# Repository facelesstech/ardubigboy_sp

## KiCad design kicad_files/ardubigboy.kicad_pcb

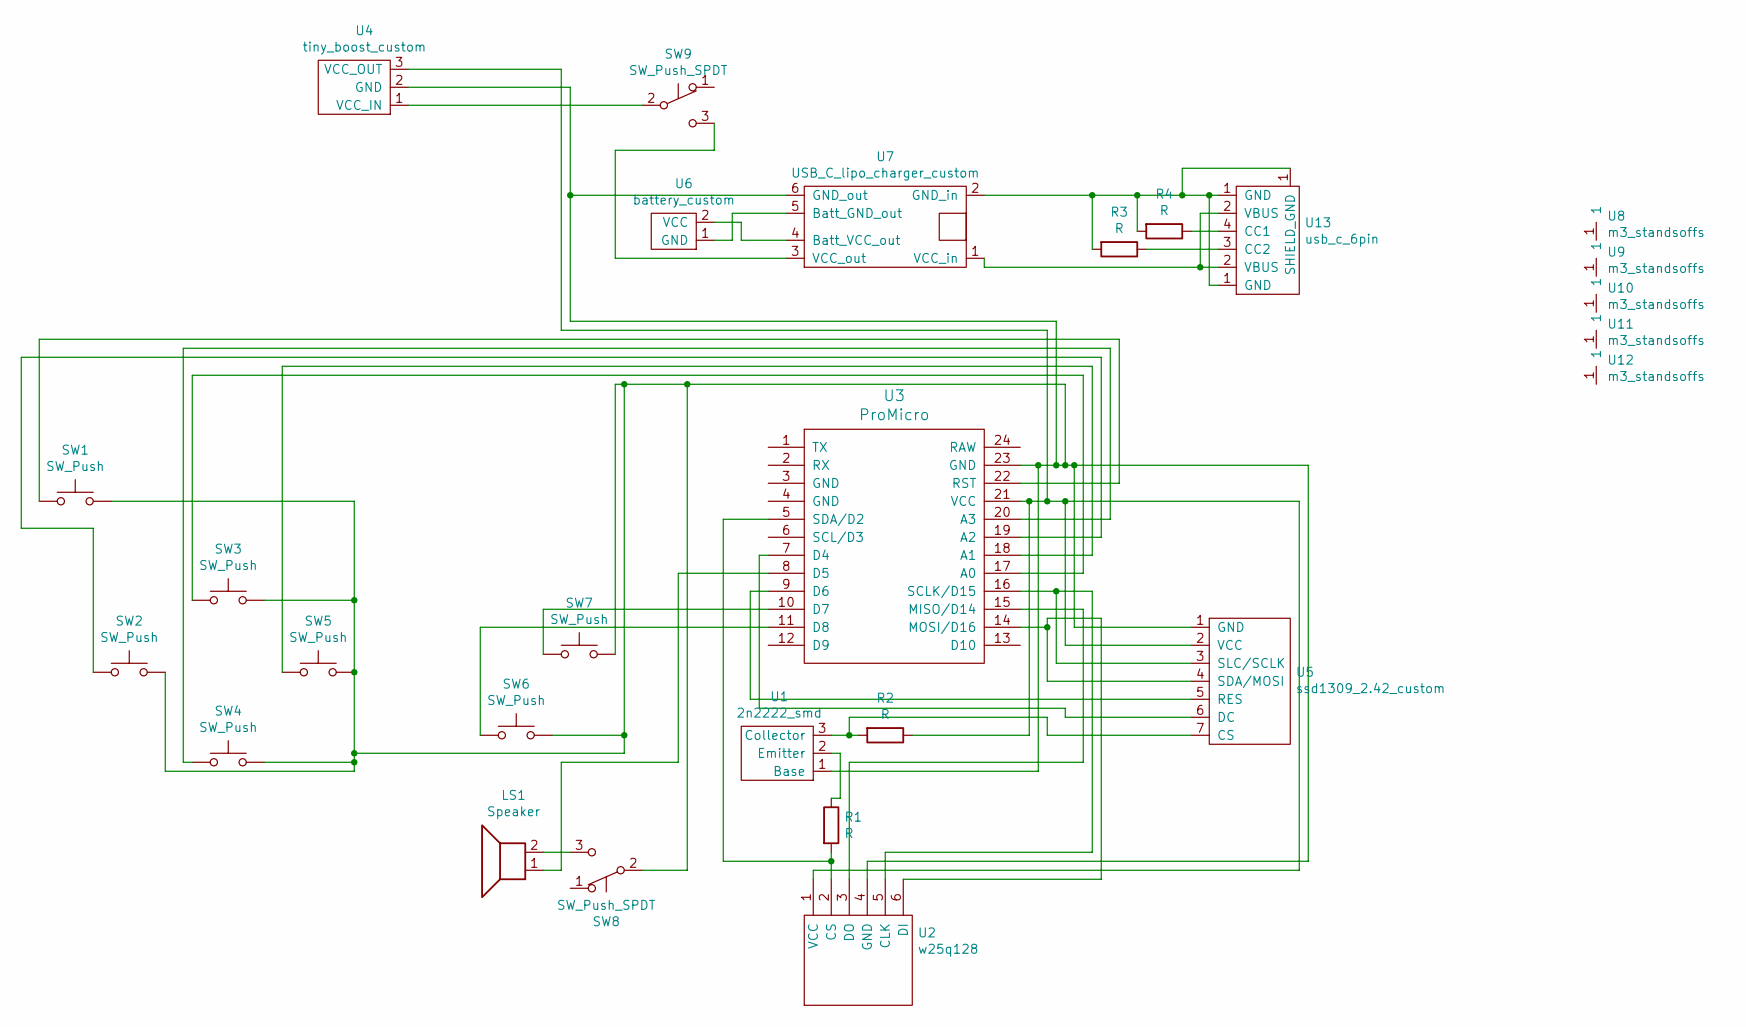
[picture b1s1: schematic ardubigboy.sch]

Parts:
LS1: Speaker; piezo_smd
R1, R2, R3, R4: R; R_1206_3216Metric_Pad1.42x1.75mm_HandSolder
SW1, SW2, SW3, SW4, SW5, SW6, SW7: SW_Push; dome_buttons_custom
SW8: SW_Push_SPDT; tiny_smd_slide_switch_adjustable
SW9: SW_Push_SPDT; 3_pin_switch_smd_side_mount
U1: 2n2222_smd; SOT-23_custom
U2: w25q128; W25Q128_smd_custom
U3: ProMicro; ProMicro_smd_pads
U4: tiny_boost_custom; Tiny_boost_orange_smd
U5: ssd1309_2.42_custom; ssd1309_2.42_custom_headers
U6: battery_custom; vcc_gnd_2pin_custom
U7: USB_C_lipo_charger_custom; USB_C_SMD_lipo_charger_custom
U8, U9, U10, U11, U12: m3_standsoffs; M4.5_custom
U13: usb_c_6pin; USB_C_6PIN_custom

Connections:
unnamed: LS1.1, U3.8 (D5)
unnamed: LS1.2, SW8.3 (C)
unnamed: R1.1, U1.2 (Emitter)
unnamed: R1.2, U2.2 (CS), U3.5 (SDA/D2)
unnamed: R2.1, U2.1 (VCC), U3.21 (VCC), U4.3 (VCC_OUT), U5.2 (VCC)
unnamed: R2.2, U1.3 (Collector), U5.7 (CS)
unnamed: R3.1, U13.3 (CC2)
unnamed: R3.2, R4.2, U7.2 (GND_in), U13.1 (GND)
unnamed: R4.1, U13.4 (CC1)
unnamed: SW1.1, U3.22 (RST)
unnamed: SW1.2, SW2.2, SW3.2, SW4.2, SW5.2, SW6.2, SW7.2, SW8.2 (B), U1.1 (Base), U2.4 (GND), U3.23 (GND), U4.2 (GND), U5.1 (GND), U7.6 (GND_out)
unnamed: SW2.1, U3.19 (A2)
unnamed: SW3.1, U3.17 (A0)
unnamed: SW4.1, U3.20 (A3)
unnamed: SW5.1, U3.18 (A1)
unnamed: SW6.1, U3.11 (D8)
unnamed: SW7.1, U3.10 (D7)
unnamed: SW9.2 (B), U4.1 (VCC_IN)
unnamed: SW9.3 (C), U7.3 (VCC_out)
unnamed: U2.3 (DO), U3.15 (MISO/D14)
unnamed: U2.5 (CLK), U3.16 (SCLK/D15), U5.3 (SLC/SCLK)
unnamed: U2.6 (DI), U3.14 (MOSI/D16), U5.4 (SDA/MOSI)
unnamed: U3.7 (D4), U5.6 (DC)
unnamed: U3.9 (D6), U5.5 (RES)
unnamed: U6.1 (GND), U7.5 (Batt_GND_out)
unnamed: U6.2 (VCC), U7.4 (Batt_VCC_out)
unnamed: U7.1 (VCC_in), U13.2 (VBUS)

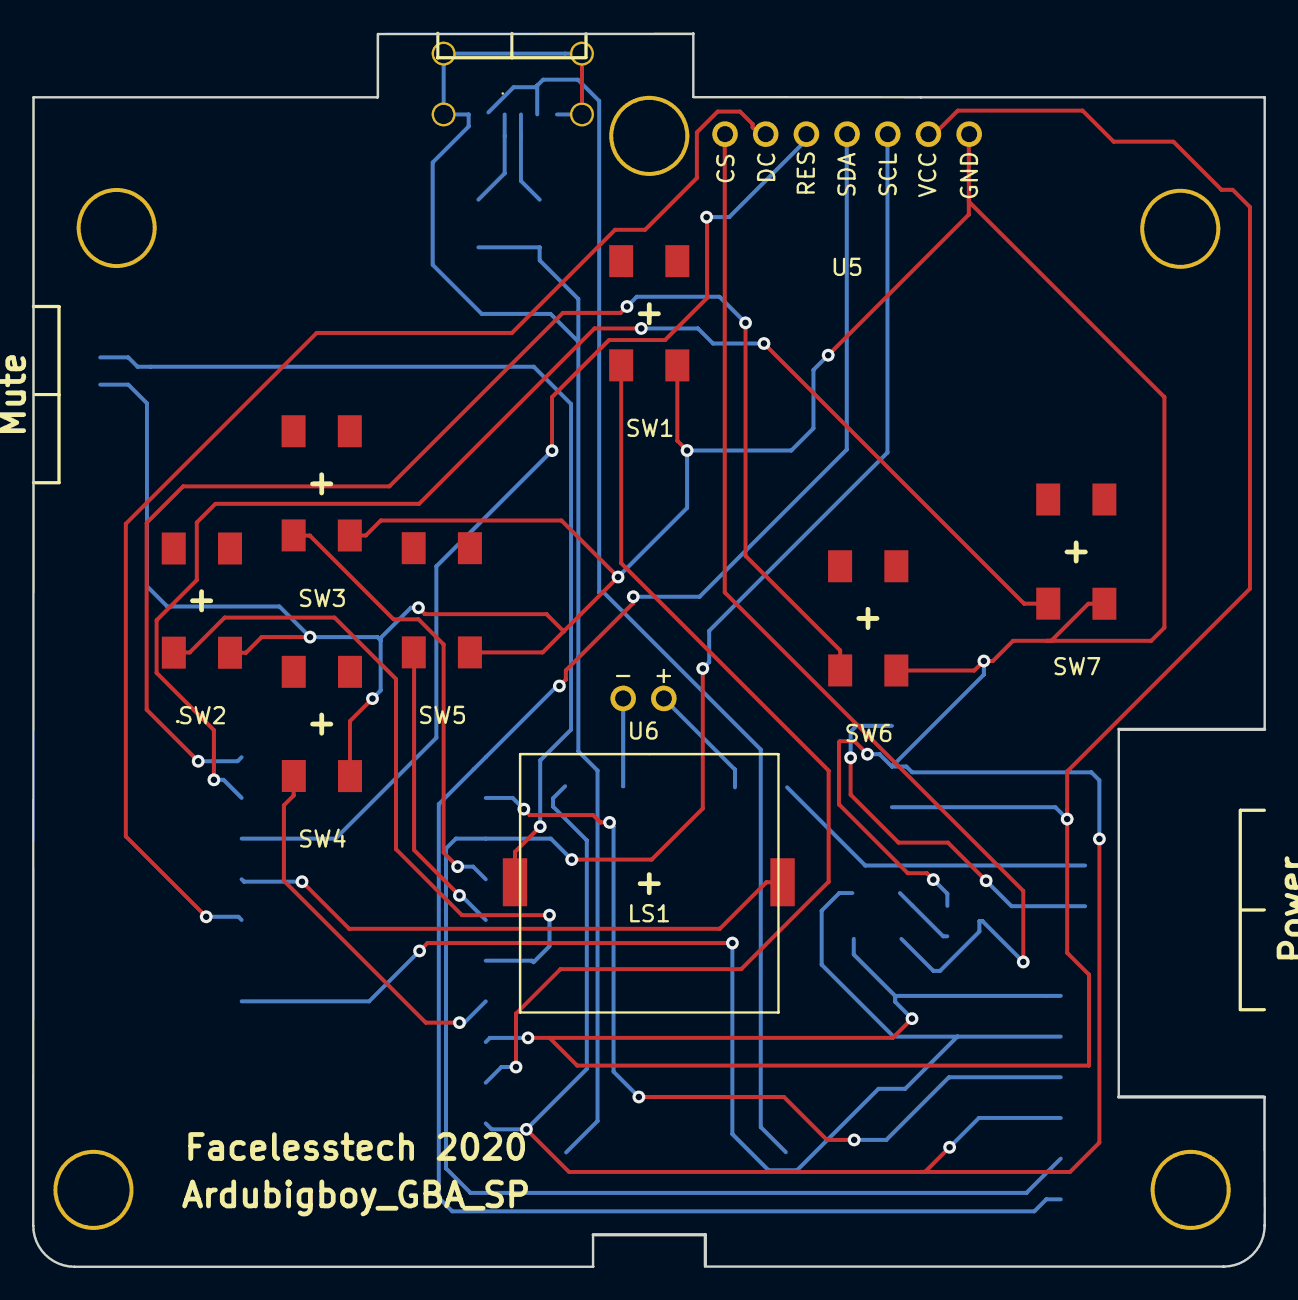
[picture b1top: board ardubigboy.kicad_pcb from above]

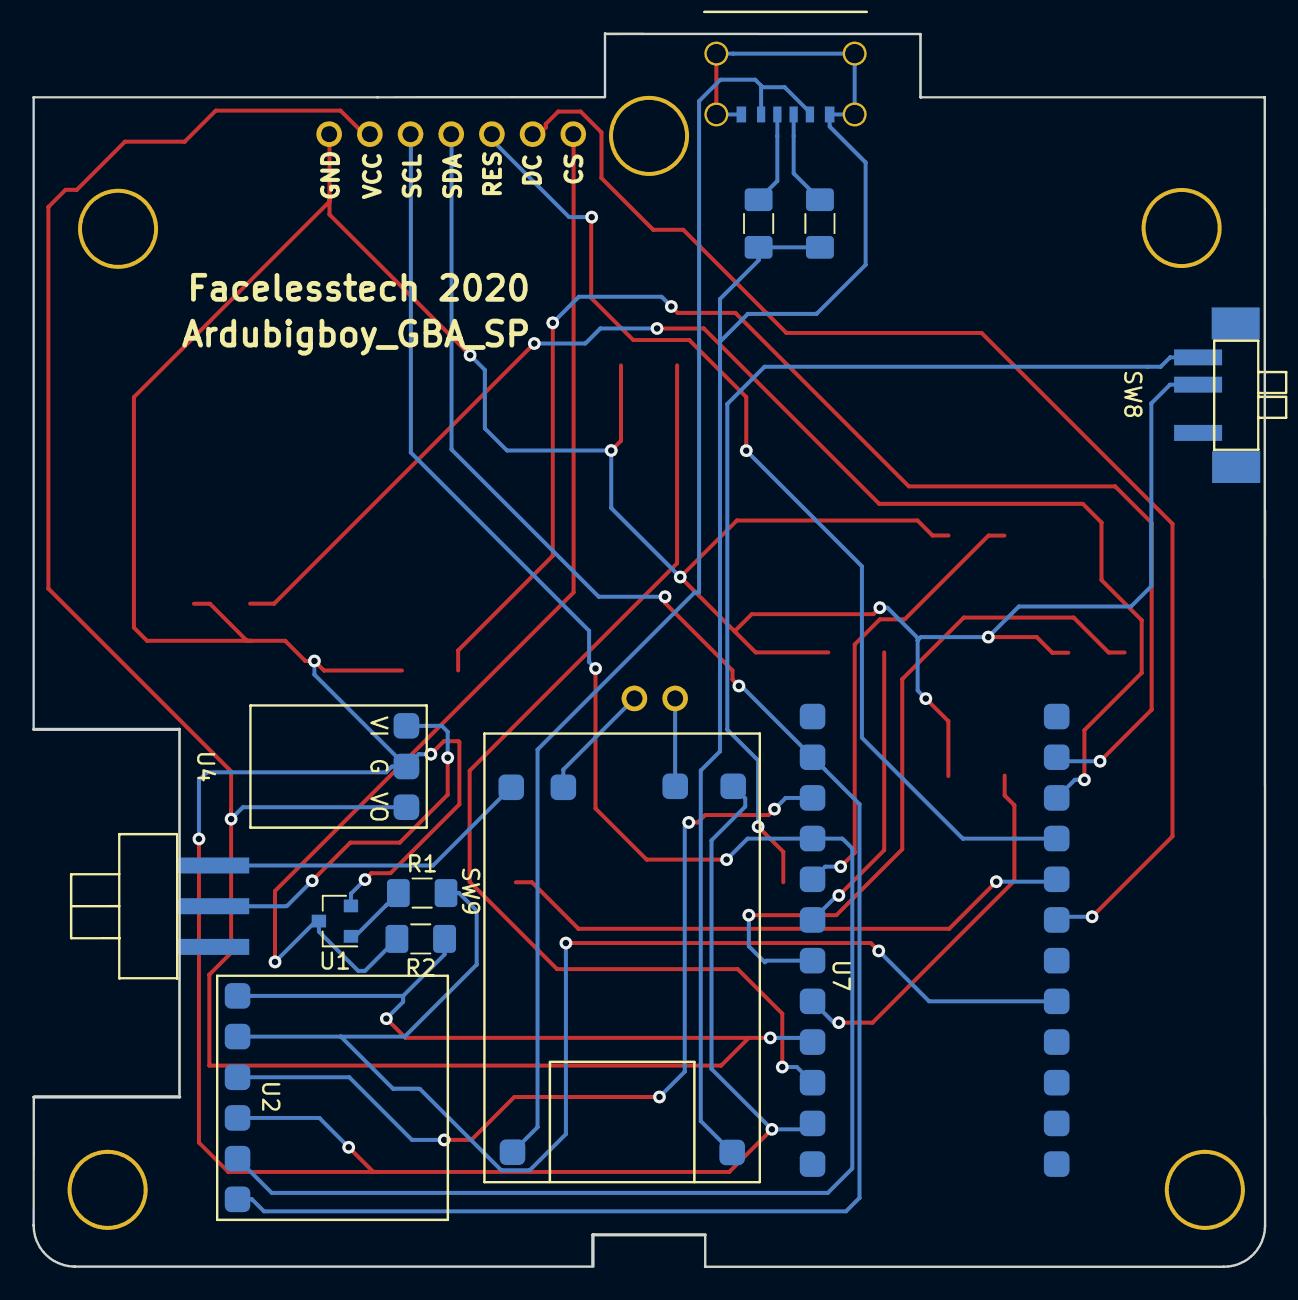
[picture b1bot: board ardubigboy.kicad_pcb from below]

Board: 2 copper layers, 76.9 x 77.0 mm, 27 parts (12 on the bottom side), 27 nets.

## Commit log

2021-01-26 PCB board files
2021-01-26 freecad and stl files
